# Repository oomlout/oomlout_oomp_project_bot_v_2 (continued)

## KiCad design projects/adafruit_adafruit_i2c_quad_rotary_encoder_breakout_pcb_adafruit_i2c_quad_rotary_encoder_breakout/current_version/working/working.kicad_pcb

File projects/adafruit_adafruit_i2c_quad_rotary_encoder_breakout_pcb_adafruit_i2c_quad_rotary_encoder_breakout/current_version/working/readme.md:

# adafruit_i2c_quad_rotary_encoder_breakout_pcb
 
## summary 
* id: adafruit_adafruit_i2c_quad_rotary_encoder_breakout_pcb_adafruit_i2c_quad_rotary_encoder_breakout
* user: adafruit
* name: adafruit_i2c_quad_rotary_encoder_breakout_pcb
* board: adafruit_i2c_quad_rotary_encoder_breakout
* repo: https://github.com/adafruit/Adafruit-I2C-Quad-Rotary-Encoder-Breakout-PCB

* src_file_repo_sch: 
* src_file_repo_sch_link: https://github.com/adafruit/Adafruit-I2C-Quad-Rotary-Encoder-Breakout-PCB/tree/main/
* full details link: https://github.com/oomlout/oomlout_oomp_project_bot_v_2/tree/main/projects/adafruit_adafruit_i2c_quad_rotary_encoder_breakout_pcb_adafruit_i2c_quad_rotary_encoder_breakout/current_version/working  

## schematic  
  
[schematic (pdf)](working_schematic.pdf) 

## pcb  

[board (pdf)](working.pdf)  

## working_bom
| Id | Designator | Footprint | Quantity | Designation | Supplier and ref |  | None | 
| --- | --- | --- | --- | --- | --- | --- | --- | 
| 1 | PLABEL9 | PLABEL9 | 1 |  |  |  | [''] | 
| 2 | D2 | CHIPLED_0603_NOOUTLINE | 1 | GREEN |  |  | [''] | 
| 3 | PLABEL10 | PLABEL10 | 1 |  |  |  | [''] | 
| 4 | CONN4,CONN3 | JST_SH4_RA | 2 | STEMMA_I2C_QTRA |  |  | [''] | 
| 5 | U$3,U$21,U$17,U$19 | MOUNTINGHOLE_2.5_PLATED | 4 | MOUNTINGHOLE2.5 |  |  | [''] | 
| 6 | JP1,JP5 | 1X06_ROUND_70 | 2 |  |  |  | [''] | 
| 7 | C1,C7,C5,C6 | 0603-NO | 4 | 1uF |  |  | [''] | 
| 8 | R7,R6,R9,R4,R3,R8,R1,R5,R2 | 0603-NO | 9 | 10K |  |  | [''] | 
| 9 | FID1,FID2 | FIDUCIAL_1MM | 2 | FIDUCIAL_1MM |  |  | [''] | 
| 10 | U$9,U$2 | ADAFRUIT_3.5MM | 2 |  |  |  | [''] | 
| 11 | D1 | CHIPLED_0603_NOOUTLINE | 1 | RED |  |  | [''] | 
| 12 | PLABEL13 | PLABEL13 | 1 |  |  |  | [''] | 
| 13 | C4 | 0603-NO | 1 | 0.1uF |  |  | [''] | 
| 14 | PLABEL7 | PLABEL7 | 1 |  |  |  | [''] | 
| 15 | U$25 | PCBFEAT-REV-040 | 1 |  |  |  | [''] | 
| 16 | PLABEL6 | PLABEL6 | 1 |  |  |  | [''] | 
| 17 | PLABEL14 | PLABEL14 | 1 |  |  |  | [''] | 
| 18 | PLABEL11 | PLABEL11 | 1 |  |  |  | [''] | 
| 19 | C2,C3 | 0805-NO | 2 | 10uF |  |  | [''] | 
| 20 | PLABEL15 | PLABEL15 | 1 |  |  |  | [''] | 
| 21 | PLABEL16 | PLABEL16 | 1 |  |  |  | [''] | 
| 22 | A1,A0,A2 | SOLDERJUMPER_CLOSEDWIRE | 3 |  |  |  | [''] | 
| 23 | PLABEL8 | PLABEL8 | 1 |  |  |  | [''] | 
| 24 | PLABEL0 | PLABEL0 | 1 |  |  |  | [''] | 
| 25 | PLABEL5 | PLABEL5 | 1 |  |  |  | [''] | 
| 26 | IC1 | QFN24_4MM | 1 | ATTINY8X7-MU |  |  | [''] | 
| 27 | PLABEL1 | PLABEL1 | 1 |  |  |  | [''] | 
| 28 | U$30,U$31 | STEMMAQT | 2 |  |  |  | [''] | 
| 29 | PLABEL4 | PLABEL4 | 1 |  |  |  | [''] | 
| 30 | PLABEL2 | PLABEL2 | 1 |  |  |  | [''] | 
| 31 | PLABEL12 | PLABEL12 | 1 |  |  |  | [''] | 
| 32 | PLABEL3 | PLABEL3 | 1 |  |  |  | [''] | 
| 33 | LED1,LED3,LED2,LED4 | NEO3535_REVERSE | 4 | WS2812B_SK6812E |  |  | [''] | 
| 34 | PLABEL20 | PLABEL20 | 1 |  |  |  | [''] | 
| 35 | PLABEL29 | PLABEL29 | 1 |  |  |  | [''] | 
| 36 | ENC4,ENC3,ENC2,ENC1 | PEC11+SWITCH | 4 |  |  |  | [''] | 
| 37 | PLABEL24 | PLABEL24 | 1 |  |  |  | [''] | 
| 38 | PLABEL27 | PLABEL27 | 1 |  |  |  | [''] | 
| 39 | PLABEL19 | PLABEL19 | 1 |  |  |  | [''] | 
| 40 | PLABEL26 | PLABEL26 | 1 |  |  |  | [''] | 
| 41 | PLABEL28 | PLABEL28 | 1 |  |  |  | [''] | 
| 42 | PLABEL32 | PLABEL32 | 1 |  |  |  | [''] | 
| 43 | PLABEL25 | PLABEL25 | 1 |  |  |  | [''] | 
| 44 | PLABEL21 | PLABEL21 | 1 |  |  |  | [''] | 
| 45 | PLABEL31 | PLABEL31 | 1 |  |  |  | [''] | 
| 46 | PLABEL30 | PLABEL30 | 1 |  |  |  | [''] | 
| 47 | PLABEL22 | PLABEL22 | 1 |  |  |  | [''] | 
| 48 | PLABEL23 | PLABEL23 | 1 |  |  |  | [''] | 
| 49 | PLABEL18 | PLABEL18 | 1 |  |  |  | [''] | 
| 50 | PLABEL17 | PLABEL17 | 1 |  |  |  | [''] | 

## bom_schematic
| Ref | Qnty | Value | Cmp name | Footprint | Description | Vendor | DNP | 
| --- | --- | --- | --- | --- | --- | --- | --- | 
| A0, A1, A2 | 3 | SOLDERJUMPERCLOSED | SOLDERJUMPERCLOSED | working:SOLDERJUMPER_CLOSEDWIRE |  |  |  | 
| C1, C5, C6, C7 | 4 | 1uF | CAP_CERAMIC0603_NO | working:0603-NO |  |  |  | 
| C2, C3 | 2 | 10uF | CAP_CERAMIC0805-NOOUTLINE | working:0805-NO |  |  |  | 
| C4 | 1 | 0.1uF | CAP_CERAMIC0603_NO | working:0603-NO |  |  |  | 
| CONN3, CONN4 | 2 | STEMMA_I2C_QTRA | STEMMA_I2C_QTRA | working:JST_SH4_RA |  |  |  | 
| D1 | 1 | RED | LED0603_NOOUTLINE | working:CHIPLED_0603_NOOUTLINE |  |  |  | 
| D2 | 1 | GREEN | LED0603_NOOUTLINE | working:CHIPLED_0603_NOOUTLINE |  |  |  | 
| ENC1, ENC2, ENC3, ENC4 | 4 | ENCODER_PLUS_SWITCH_PEC11 | ENCODER_PLUS_SWITCH_PEC11 | working:PEC11+SWITCH |  |  |  | 
| FID1, FID2 | 2 | FIDUCIAL_1MM | FIDUCIAL_1MM | working:FIDUCIAL_1MM |  |  |  | 
| IC1 | 1 | ATTINY8X7-MU | ATTINY8X7-MU | working:QFN24_4MM |  |  |  | 
| JP1, JP5 | 2 | HEADER-1X670MIL | HEADER-1X670MIL | working:1X06_ROUND_70 |  |  |  | 
| LED1, LED2, LED3, LED4 | 4 | WS2812B_SK6812E | WS2812B_SK6812E | working:NEO3535_REVERSE |  |  |  | 
| R1, R2, R3, R4, R5, R6, R7, R8, R9 | 9 | 10K | RESISTOR_0603_NOOUT | working:0603-NO |  |  |  | 
| U$3, U$17, U$19, U$21 | 4 | MOUNTINGHOLE2.5 | MOUNTINGHOLE2.5 | working:MOUNTINGHOLE_2.5_PLATED |  |  |  | 

## mounting_holes
| x | y | package | value | ref | size | 
| --- | --- | --- | --- | --- | --- | 
| 38.1 | 16.51 | MOUNTINGHOLE_2.5_PLATED | MOUNTINGHOLE2.5 | U$3 | m3 | 
| 0.0 | 16.51 | MOUNTINGHOLE_2.5_PLATED | MOUNTINGHOLE2.5 | U$17 | m3 | 
| 38.1 | 0.0 | MOUNTINGHOLE_2.5_PLATED | MOUNTINGHOLE2.5 | U$19 | m3 | 
| 0.0 | 0.0 | MOUNTINGHOLE_2.5_PLATED | MOUNTINGHOLE2.5 | U$21 | m3 |

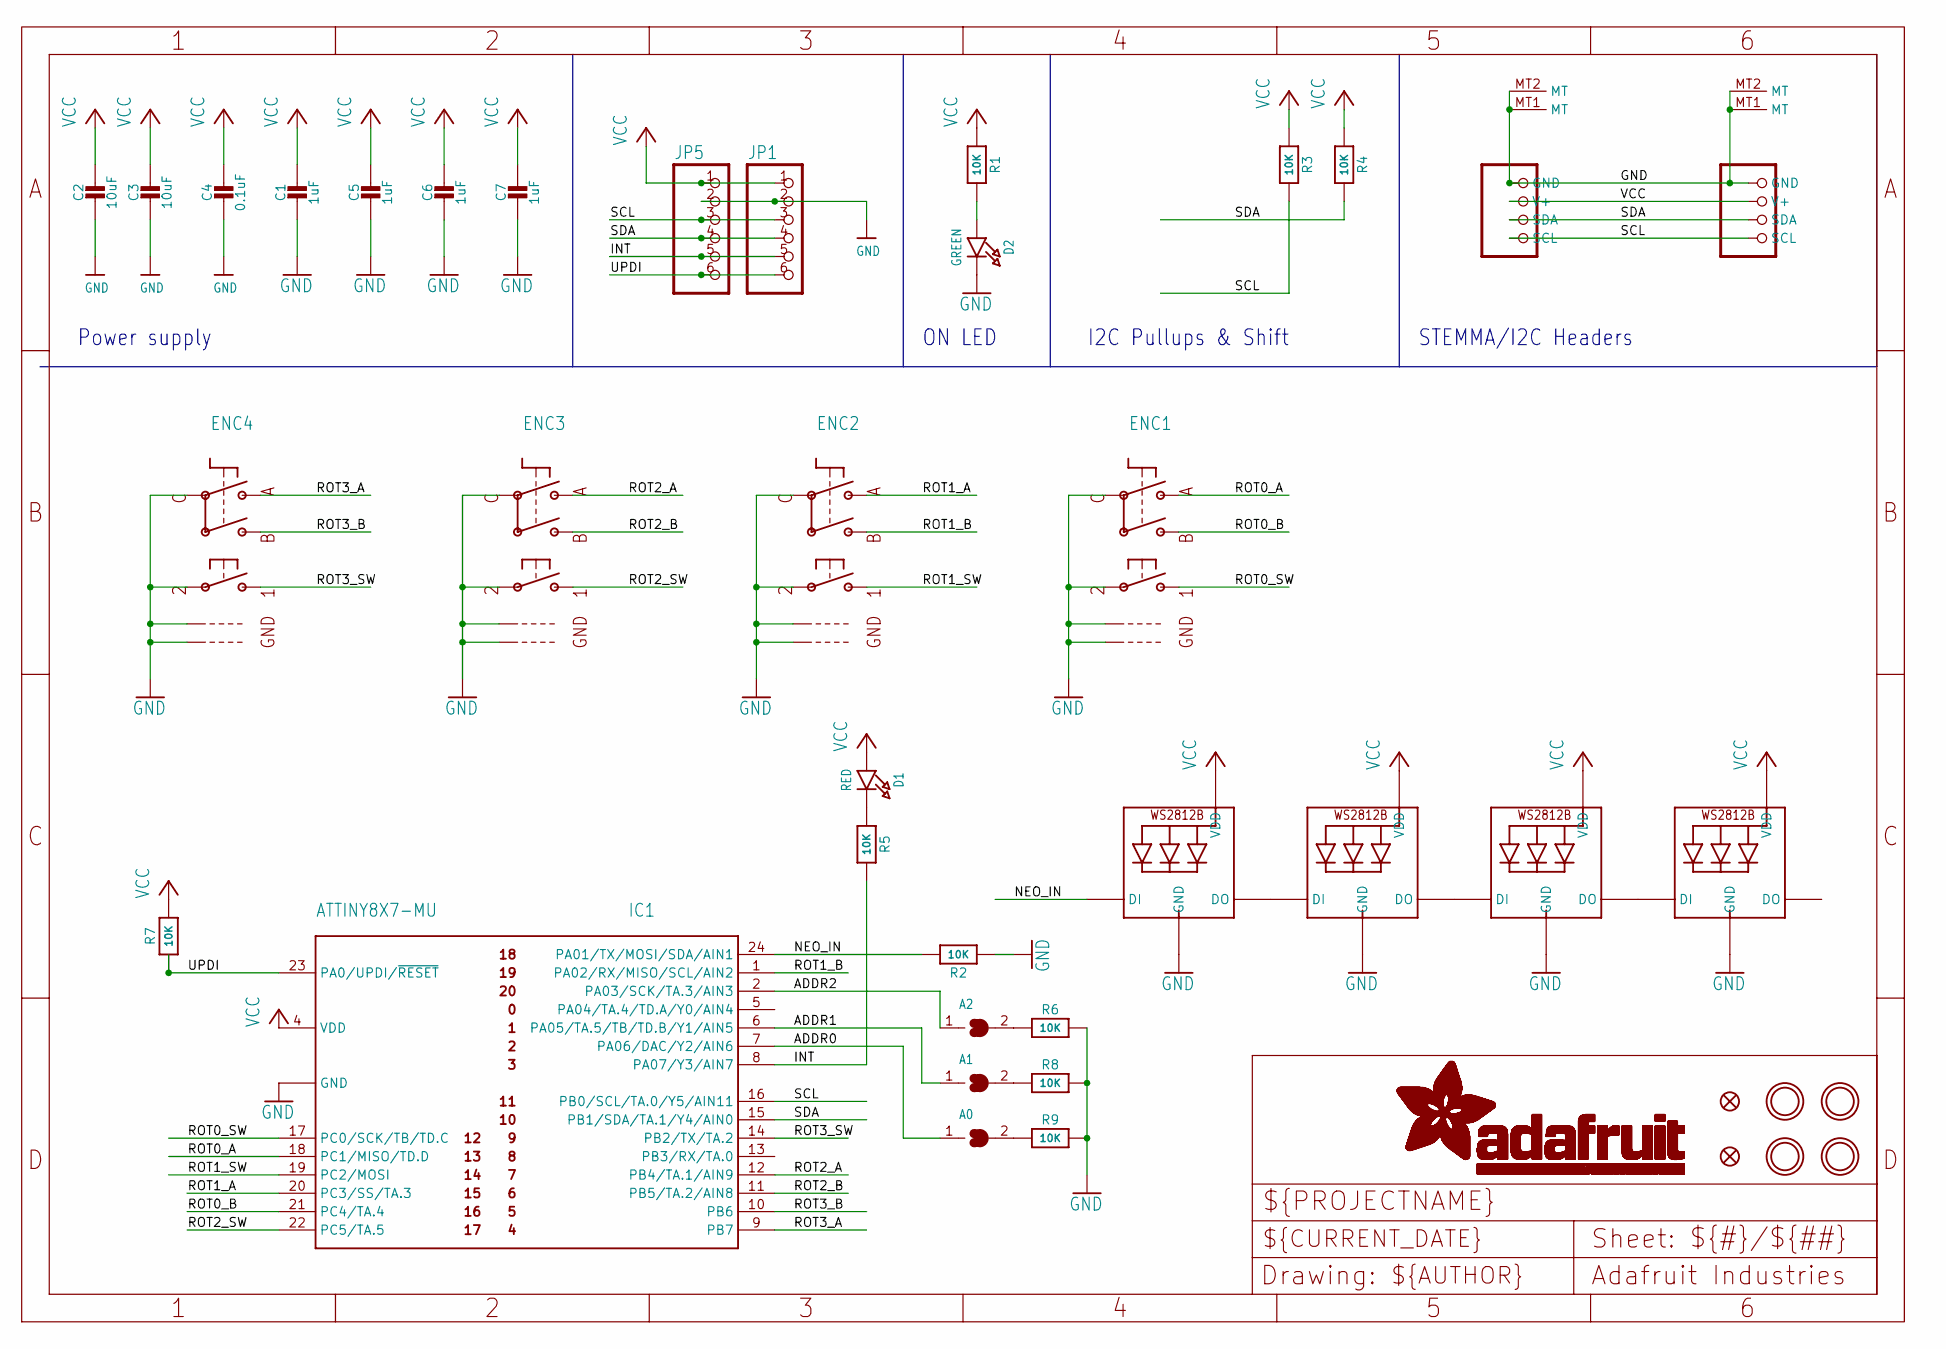
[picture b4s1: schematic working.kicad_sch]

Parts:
A0, A1, A2: SOLDERJUMPERCLOSED; SOLDERJUMPER_CLOSEDWIRE
C1, C5, C6, C7: 1uF; 0603-NO
C2, C3: 10uF; 0805-NO
C4: 0.1uF; 0603-NO
CONN3, CONN4: STEMMA_I2C_QTRA; JST_SH4_RA
D1: RED; CHIPLED_0603_NOOUTLINE
D2: GREEN; CHIPLED_0603_NOOUTLINE
ENC1, ENC2, ENC3, ENC4: ENCODER_PLUS_SWITCH_PEC11; PEC11+SWITCH
FID1, FID2: FIDUCIAL_1MM
IC1: ATTINY8X7-MU; QFN24_4MM
JP1, JP5: HEADER-1X670MIL; 1X06_ROUND_70
LED1, LED2, LED3, LED4: WS2812B_SK6812E; NEO3535_REVERSE
R1, R2, R3, R4, R5, R6, R7, R8, R9: 10K; 0603-NO
U$3, U$17, U$19, U$21: MOUNTINGHOLE2.5; MOUNTINGHOLE_2.5_PLATED

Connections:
ADDR0: A0.1, IC1.7 (PA06/DAC/Y2/AIN6)
ADDR1: A1.1, IC1.6 (PA05/TA.5/TB/TD.B/Y1/AIN5)
ADDR2: A2.1, IC1.2 (PA03/SCK/TA.3/AIN3)
GND: C1.2, C2.2, C3.2, C4.2, C5.2, C6.2, C7.2, CONN3.1 (GND), CONN3.MT1 (MT), CONN3.MT2 (MT), CONN4.1 (GND), CONN4.MT1 (MT), CONN4.MT2 (MT), D2.C, ENC1.P$2, ENC1.P$C, ENC1.P$GND1, ENC1.P$GND2, ENC2.P$2, ENC2.P$C, ENC2.P$GND1, ENC2.P$GND2, ENC3.P$2, ENC3.P$C, ENC3.P$GND1, ENC3.P$GND2, ENC4.P$2, ENC4.P$C, ENC4.P$GND1, ENC4.P$GND2, IC1.3 (GND), IC1.THERM (GND), JP1.2, JP5.2, LED1.3-GND (GND), LED2.3-GND (GND), LED3.3-GND (GND), LED4.3-GND (GND), R2.1, R6.2, R8.2, R9.2
INT: IC1.8 (PA07/Y3/AIN7), JP1.5, JP5.5, R5.2
unnamed: D2.A, R1.2
unnamed: LED1.2-DOUT (DO), LED2.4-DIN (DI)
unnamed: LED2.2-DOUT (DO), LED3.4-DIN (DI)
unnamed: LED3.2-DOUT (DO), LED4.4-DIN (DI)
unnamed: D1.C, R5.1
unnamed: A2.2, R6.1
unnamed: A1.2, R8.1
unnamed: A0.2, R9.1
NEO_IN: IC1.24 (PA01/TX/MOSI/SDA/AIN1), LED1.4-DIN (DI), R2.2
ROT0_A: ENC1.P$A, IC1.18 (PC1/MISO/TD.D)
ROT0_B: ENC1.P$B, IC1.21 (PC4/TA.4)
ROT0_SW: ENC1.P$1, IC1.17 (PC0/SCK/TB/TD.C)
ROT1_A: ENC2.P$A, IC1.20 (PC3/SS/TA.3)
ROT1_B: ENC2.P$B, IC1.1 (PA02/RX/MISO/SCL/AIN2)
ROT1_SW: ENC2.P$1, IC1.19 (PC2/MOSI)
ROT2_A: ENC3.P$A, IC1.12 (PB4/TA.1/AIN9)
ROT2_B: ENC3.P$B, IC1.11 (PB5/TA.2/AIN8)
ROT2_SW: ENC3.P$1, IC1.22 (PC5/TA.5)
ROT3_A: ENC4.P$A, IC1.9 (PB7)
ROT3_B: ENC4.P$B, IC1.10 (PB6)
ROT3_SW: ENC4.P$1, IC1.14 (PB2/TX/TA.2)
SCL: CONN3.4 (SCL), CONN4.4 (SCL), IC1.16 (PB0/SCL/TA.0/Y5/AIN11), JP1.3, JP5.3, R3.2
SDA: CONN3.3 (SDA), CONN4.3 (SDA), IC1.15 (PB1/SDA/TA.1/Y4/AIN0), JP1.4, JP5.4, R4.2
UPDI: IC1.23 (PA0/UPDI/~RESET), JP1.6, JP5.6, R7.1
VCC: C1.1, C2.1, C3.1, C4.1, C5.1, C6.1, C7.1, CONN3.2 (V+), CONN4.2 (V+), D1.A, IC1.4 (VDD), JP1.1, JP5.1, LED1.1-VDD (VDD), LED2.1-VDD (VDD), LED3.1-VDD (VDD), LED4.1-VDD (VDD), R1.1, R3.1, R4.1, R7.2

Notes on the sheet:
STEMMA/I2C Headers
I2C Pullups & Shift
Power supply
ON LED

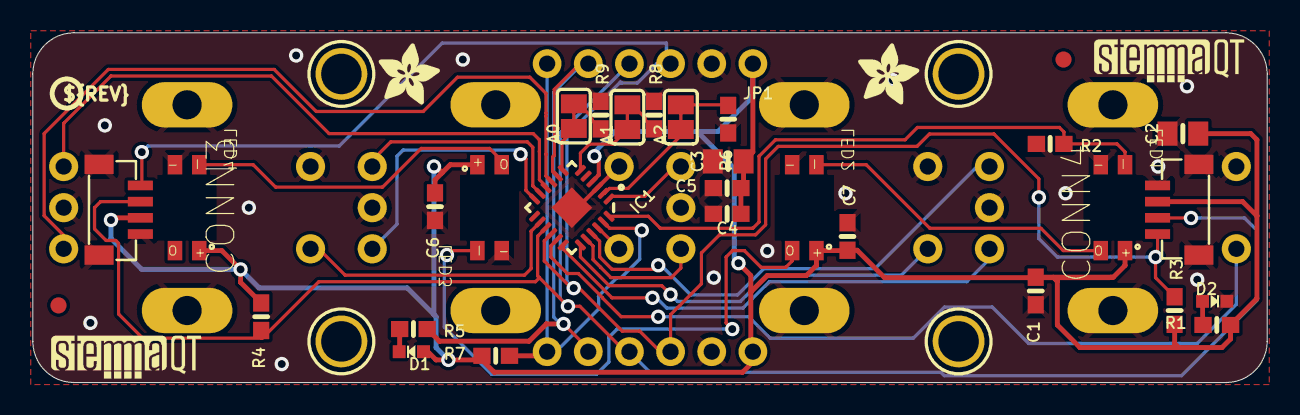
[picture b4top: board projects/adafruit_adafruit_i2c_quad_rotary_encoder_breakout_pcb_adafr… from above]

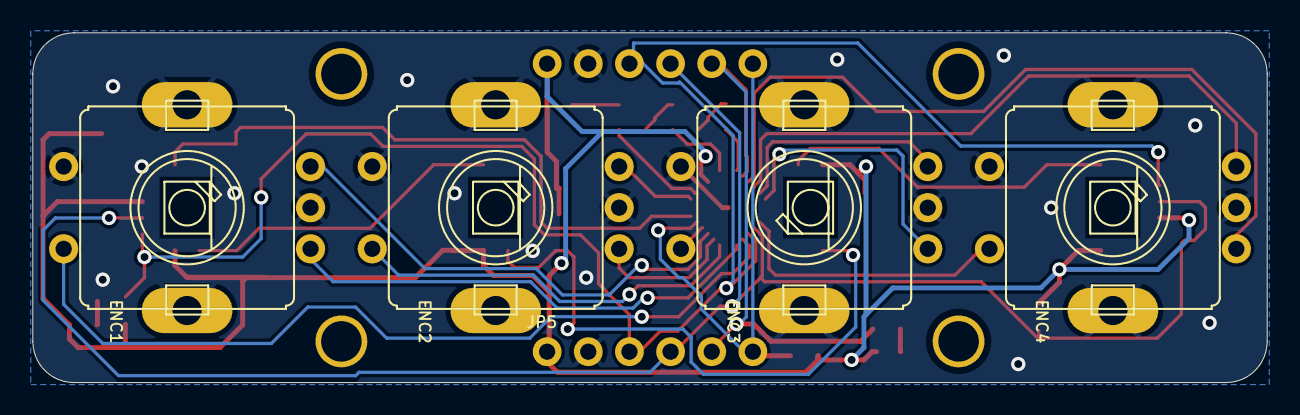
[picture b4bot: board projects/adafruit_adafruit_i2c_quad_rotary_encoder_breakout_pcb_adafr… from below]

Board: 2 copper layers, 76.2 x 21.6 mm, 78 parts (25 on the bottom side), 30 nets.

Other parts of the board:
PLABEL0: PLABEL0
PLABEL1: PLABEL1
PLABEL2: PLABEL2
PLABEL3: PLABEL3
PLABEL4: PLABEL4
PLABEL5: PLABEL5
PLABEL6: PLABEL6
PLABEL7: PLABEL7
PLABEL8: PLABEL8
PLABEL9: PLABEL9
PLABEL10: PLABEL10
PLABEL11: PLABEL11
PLABEL12: PLABEL12
PLABEL13: PLABEL13
PLABEL14: PLABEL14
PLABEL15: PLABEL15
PLABEL16: PLABEL16
PLABEL17: PLABEL17
PLABEL18: PLABEL18
PLABEL19: PLABEL19
PLABEL20: PLABEL20
PLABEL21: PLABEL21
PLABEL22: PLABEL22
PLABEL23: PLABEL23
PLABEL24: PLABEL24
PLABEL25: PLABEL25
PLABEL26: PLABEL26
PLABEL27: PLABEL27
PLABEL28: PLABEL28
PLABEL29: PLABEL29
PLABEL30: PLABEL30
PLABEL31: PLABEL31
PLABEL32: PLABEL32
U$2, U$9: ADAFRUIT_3.5MM
U$25: PCBFEAT-REV-040
U$30, U$31: STEMMAQT

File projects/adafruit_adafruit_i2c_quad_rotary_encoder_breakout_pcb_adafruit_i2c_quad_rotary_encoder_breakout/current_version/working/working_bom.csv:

"Id";"Designator";"Footprint";"Quantity";"Designation";"Supplier and ref";
1;"PLABEL9";"PLABEL9";1;"";;;
2;"D2";"CHIPLED_0603_NOOUTLINE";1;"GREEN";;;
3;"PLABEL10";"PLABEL10";1;"";;;
4;"CONN4,CONN3";"JST_SH4_RA";2;"STEMMA_I2C_QTRA";;;
5;"U$3,U$21,U$17,U$19";"MOUNTINGHOLE_2.5_PLATED";4;"MOUNTINGHOLE2.5";;;
6;"JP1,JP5";"1X06_ROUND_70";2;"";;;
7;"C1,C7,C5,C6";"0603-NO";4;"1uF";;;
8;"R7,R6,R9,R4,R3,R8,R1,R5,R2";"0603-NO";9;"10K";;;
9;"FID1,FID2";"FIDUCIAL_1MM";2;"FIDUCIAL_1MM";;;
10;"U$9,U$2";"ADAFRUIT_3.5MM";2;"";;;
11;"D1";"CHIPLED_0603_NOOUTLINE";1;"RED";;;
12;"PLABEL13";"PLABEL13";1;"";;;
13;"C4";"0603-NO";1;"0.1uF";;;
14;"PLABEL7";"PLABEL7";1;"";;;
15;"U$25";"PCBFEAT-REV-040";1;"";;;
16;"PLABEL6";"PLABEL6";1;"";;;
17;"PLABEL14";"PLABEL14";1;"";;;
18;"PLABEL11";"PLABEL11";1;"";;;
19;"C2,C3";"0805-NO";2;"10uF";;;
20;"PLABEL15";"PLABEL15";1;"";;;
21;"PLABEL16";"PLABEL16";1;"";;;
22;"A1,A0,A2";"SOLDERJUMPER_CLOSEDWIRE";3;"";;;
23;"PLABEL8";"PLABEL8";1;"";;;
24;"PLABEL0";"PLABEL0";1;"";;;
25;"PLABEL5";"PLABEL5";1;"";;;
26;"IC1";"QFN24_4MM";1;"ATTINY8X7-MU";;;
27;"PLABEL1";"PLABEL1";1;"";;;
28;"U$30,U$31";"STEMMAQT";2;"";;;
29;"PLABEL4";"PLABEL4";1;"";;;
30;"PLABEL2";"PLABEL2";1;"";;;
31;"PLABEL12";"PLABEL12";1;"";;;
32;"PLABEL3";"PLABEL3";1;"";;;
33;"LED1,LED3,LED2,LED4";"NEO3535_REVERSE";4;"WS2812B_SK6812E";;;
34;"PLABEL20";"PLABEL20";1;"";;;
35;"PLABEL29";"PLABEL29";1;"";;;
36;"ENC4,ENC3,ENC2,ENC1";"PEC11+SWITCH";4;"";;;
37;"PLABEL24";"PLABEL24";1;"";;;
38;"PLABEL27";"PLABEL27";1;"";;;
39;"PLABEL19";"PLABEL19";1;"";;;
40;"PLABEL26";"PLABEL26";1;"";;;
41;"PLABEL28";"PLABEL28";1;"";;;
42;"PLABEL32";"PLABEL32";1;"";;;
43;"PLABEL25";"PLABEL25";1;"";;;
44;"PLABEL21";"PLABEL21";1;"";;;
45;"PLABEL31";"PLABEL31";1;"";;;
46;"PLABEL30";"PLABEL30";1;"";;;
47;"PLABEL22";"PLABEL22";1;"";;;
48;"PLABEL23";"PLABEL23";1;"";;;
49;"PLABEL18";"PLABEL18";1;"";;;
50;"PLABEL17";"PLABEL17";1;"";;;

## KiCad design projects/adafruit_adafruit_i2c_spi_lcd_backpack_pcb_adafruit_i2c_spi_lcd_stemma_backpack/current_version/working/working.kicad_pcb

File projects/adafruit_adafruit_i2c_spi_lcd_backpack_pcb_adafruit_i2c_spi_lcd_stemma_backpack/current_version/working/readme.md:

# adafruit_i2c_spi_lcd_backpack_pcb
 
## summary 
* id: adafruit_adafruit_i2c_spi_lcd_backpack_pcb_adafruit_i2c_spi_lcd_stemma_backpack
* user: adafruit
* name: adafruit_i2c_spi_lcd_backpack_pcb
* board: adafruit_i2c_spi_lcd_stemma_backpack
* repo: https://github.com/adafruit/Adafruit-I2C-SPI-LCD-Backpack-PCB

* src_file_repo_sch: 
* src_file_repo_sch_link: https://github.com/adafruit/Adafruit-I2C-SPI-LCD-Backpack-PCB/tree/master/
* full details link: https://github.com/oomlout/oomlout_oomp_project_bot_v_2/tree/main/projects/adafruit_adafruit_i2c_spi_lcd_backpack_pcb_adafruit_i2c_spi_lcd_stemma_backpack/current_version/working  

## schematic  
  
[schematic (pdf)](working_schematic.pdf) 

## pcb  

[board (pdf)](working.pdf)  

## working_bom
| Id | Designator | Footprint | Quantity | Designation | Supplier and ref |  | None | 
| --- | --- | --- | --- | --- | --- | --- | --- | 
| 1 | A0,A1,A2,SPIEN0 | SOLDERJUMPER_ARROW_NOPASTE | 4 |  |  |  | [''] | 
| 2 | PLABEL3 | PLABEL3 | 1 |  |  |  | [''] | 
| 3 | PLABEL2 | PLABEL2 | 1 |  |  |  | [''] | 
| 4 | U$1,U$2 | FIDUCIAL_1MM | 2 | FIDUCIAL |  |  | [''] | 
| 5 | C1,C2 | 0603-NO | 2 | 0.1uF |  |  | [''] | 
| 6 | PLABEL4 | PLABEL4 | 1 |  |  |  | [''] | 
| 7 | CONN4,CONN3 | JST_SH4 | 2 | STEMMA_I2C_QT |  |  | [''] | 
| 8 | R1,R6 | 0603-NO | 2 | 10K |  |  | [''] | 
| 9 | PLABEL5 | PLABEL5 | 1 |  |  |  | [''] | 
| 10 | R8,R3 | RESPACK_4X0603 | 2 | 4.7K Pack |  |  | [''] | 
| 11 | PLABEL0 | PLABEL0 | 1 |  |  |  | [''] | 
| 12 | PLABEL8 | PLABEL8 | 1 |  |  |  | [''] | 
| 13 | SJ1 | SOLDERJUMPER_CLOSEDWIRE | 1 |  |  |  | [''] | 
| 14 | PLABEL1 | PLABEL1 | 1 |  |  |  | [''] | 
| 15 | D1 | CHIPLED_0603_NOOUTLINE | 1 | GREEN |  |  | [''] | 
| 16 | C5,C4 | 0805-NO | 2 | 10uF |  |  | [''] | 
| 17 | PLABEL7 | PLABEL7 | 1 |  |  |  | [''] | 
| 18 | U$4 | ADAFRUIT_3.5MM | 1 |  |  |  | [''] | 
| 19 | U$7 | PCBFEAT-REV-040 | 1 |  |  |  | [''] | 
| 20 | PLABEL11 | PLABEL11 | 1 |  |  |  | [''] | 
| 21 | J1 | 1X05-3.5MM | 1 | 1X5 |  |  | [''] | 
| 22 | JP1 | 1X16 | 1 |  |  |  | [''] | 
| 23 | C6 | 0805-NO | 1 | 1uF |  |  | [''] | 
| 24 | IC3 | SOT23-6 | 1 | AP3602/RT9361 |  |  | [''] | 
| 25 | Q2,Q1 | SOT363 | 2 | BSS138 |  |  | [''] | 
| 26 | PLABEL9 | PLABEL9 | 1 |  |  |  | [''] | 
| 27 | IC1 | SO18W | 1 | MCP23008/SO |  |  | [''] | 
| 28 | @HOLE1,@HOLE0 |  | 2 |  |  |  | [''] | 
| 29 | PLABEL10 | PLABEL10 | 1 |  |  |  | [''] | 
| 30 | IC2 | SO16 | 1 | 74HC595D |  |  | [''] | 
| 31 | R2 | RTRIM3314J | 1 | 3314J-1-104E |  |  | [''] | 
| 32 | PLABEL6 | PLABEL6 | 1 |  |  |  | [''] | 
| 33 | TP2,TP4,TP3,TP1 | TESTPOINT_ROUND_1.5MM | 4 |  |  |  | [''] | 
| 34 | U$11,U$12 | STEMMAQT | 2 |  |  |  | [''] | 
| 35 | PLABEL12 | PLABEL12 | 1 |  |  |  | [''] | 
| 36 | U$23 | ADAFRUIT_TEXT_20MM | 1 |  |  |  | [''] | 

## bom_schematic
| Ref | Qnty | Value | Cmp name | Footprint | Description | Vendor | DNP | 
| --- | --- | --- | --- | --- | --- | --- | --- | 
| A0, A1, A2 | 3 | SOLDERJUMPER | SOLDERJUMPER | working:SOLDERJUMPER_ARROW_NOPASTE |  |  |  | 
| C1, C2 | 2 | 0.1uF | CAP_CERAMIC0603_NO | working:0603-NO |  |  |  | 
| C4, C5 | 2 | 10uF | CAP_CERAMIC0805-NOOUTLINE | working:0805-NO |  |  |  | 
| C6 | 1 | 1uF | CAP_CERAMIC0805-NOOUTLINE | working:0805-NO |  |  |  | 
| CONN3, CONN4 | 2 | STEMMA_I2C_QT | STEMMA_I2C_QT | working:JST_SH4 |  |  |  | 
| D1 | 1 | GREEN | LED0603_NOOUTLINE | working:CHIPLED_0603_NOOUTLINE |  |  |  | 
| IC1 | 1 | MCP23008/SO | MCP23008/SO | working:SO18W |  |  |  | 
| IC2 | 1 | 74595D | 74595D | working:SO16 |  |  |  | 
| IC3 | 1 | AP3602 | AP3602 | working:SOT23-6 |  |  |  | 
| J1 | 1 | 1X5 | 1X5 | working:1X05-3.5MM |  |  |  | 
| JP1 | 1 | PINHD-1X16 | PINHD-1X16 | working:1X16 |  |  |  | 
| Q1, Q2 | 2 | BSS138 | MOSFET-N_DUAL | working:SOT363 |  |  |  | 
| R1, R6 | 2 | 10K | RESISTOR_0603_NOOUT | working:0603-NO |  |  |  | 
| R2 | 1 | 3314J-1-104E | R-TRIMM3314J | working:RTRIM3314J |  |  |  | 
| R3, R8 | 2 | 4.7K Pack | RESISTOR_4PACK | working:RESPACK_4X0603 |  |  |  | 
| SJ1 | 1 | SOLDERJUMPERCLOSED | SOLDERJUMPERCLOSED | working:SOLDERJUMPER_CLOSEDWIRE |  |  |  | 
| SPIEN0 | 1 | SOLDERJUMPER | SOLDERJUMPER | working:SOLDERJUMPER_ARROW_NOPASTE |  |  |  | 
| TP1, TP2, TP3, TP4 | 4 | TESTPOINTROUND1.5MM | TESTPOINTROUND1.5MM | working:TESTPOINT_ROUND_1.5MM |  |  |  | 
| U$1, U$2 | 2 | FIDUCIAL | FIDUCIAL | working:FIDUCIAL_1MM |  |  |  |

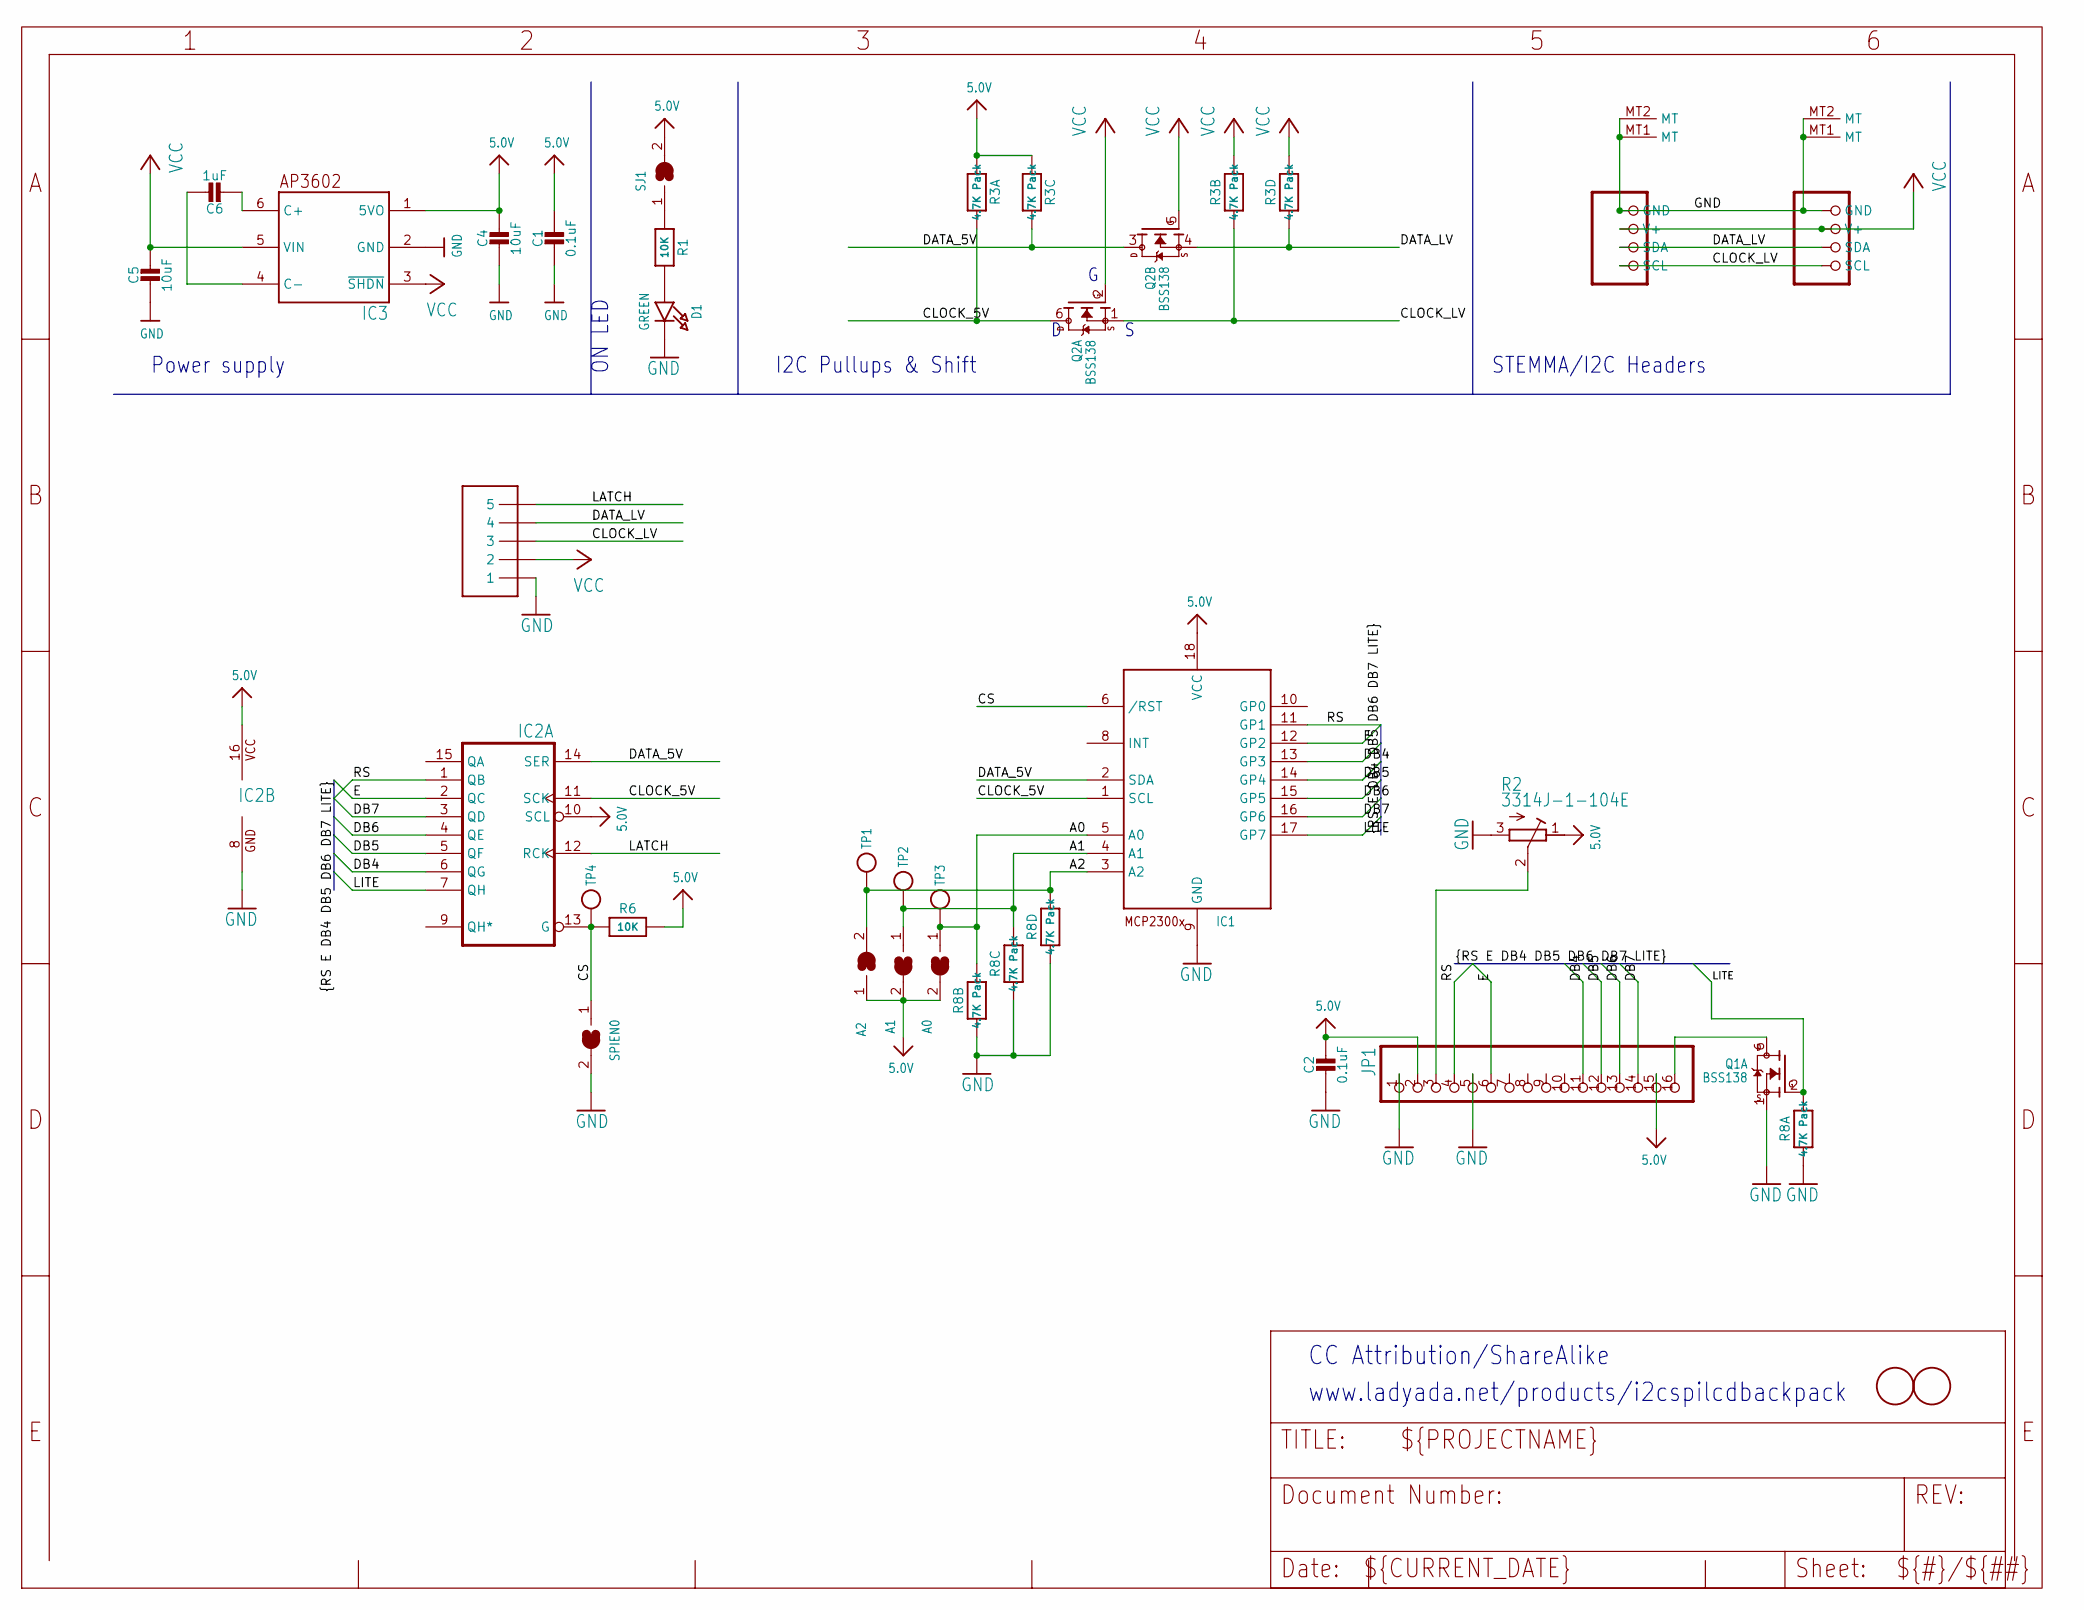
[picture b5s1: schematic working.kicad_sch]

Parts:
A0, A1, A2: SOLDERJUMPER; SOLDERJUMPER_ARROW_NOPASTE
C1, C2: 0.1uF; 0603-NO
C4, C5: 10uF; 0805-NO
C6: 1uF; 0805-NO
CONN3, CONN4: STEMMA_I2C_QT; JST_SH4
D1: GREEN; CHIPLED_0603_NOOUTLINE
IC1: MCP23008/SO; SO18W
IC2: 74595D; SO16
IC3: AP3602; SOT23-6
J1: 1X5; 1X05-3.5MM
JP1: PINHD-1X16; 1X16
Q1, Q2: BSS138; SOT363
R1, R6: 10K; 0603-NO
R2: 3314J-1-104E; RTRIM3314J
R3, R8: 4.7K Pack; RESPACK_4X0603
SJ1: SOLDERJUMPERCLOSED; SOLDERJUMPER_CLOSEDWIRE
SPIEN0: SOLDERJUMPER; SOLDERJUMPER_ARROW_NOPASTE
TP1, TP2, TP3, TP4: TESTPOINTROUND1.5MM; TESTPOINT_ROUND_1.5MM
U$1, U$2: FIDUCIAL; FIDUCIAL_1MM

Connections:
5.0V: A0.2, A1.2, A2.1, C1.1, C2.1, C4.1, IC1.18 (VCC), IC2.10 (SCL), IC2.16 (VCC), IC3.1 (5VO), JP1.2, JP1.15, R2.1 (E), R3.1, R3.3 (1), R6.1, SJ1.2
A0: A0.1, IC1.5 (A0), R8.7 (2), TP3.P$1
A1: A1.1, IC1.4 (A1), R8.6 (2), TP2.P$1
A2: A2.2, IC1.3 (A2), R8.5 (2), TP1.P$1
CLOCK_5V: IC1.1 (SCL), IC2.11 (SCK), Q2.6 (D), R3.8 (2)
CLOCK_LV: CONN3.4 (SCL), CONN4.4 (SCL), J1.3, Q2.1 (S), R3.7 (2)
CONTRAST: JP1.3, R2.2 (S)
CS: IC1.6 (/RST), IC2.13 (G), R6.2, SPIEN0.1, TP4.P$1
DATA_5V: IC1.2 (SDA), IC2.14 (SER), Q2.3 (D), R3.6 (2)
DATA_LV: CONN3.3 (SDA), CONN4.3 (SDA), J1.4, Q2.4 (S), R3.5 (2)
DB4: IC1.13 (GP3), IC2.6 (QG), JP1.11
DB5: IC1.14 (GP4), IC2.5 (QF), JP1.12
DB6: IC1.15 (GP5), IC2.4 (QE), JP1.13
DB7: IC1.16 (GP6), IC2.3 (QD), JP1.14
E: IC1.12 (GP2), IC2.2 (QC), JP1.6
GND: C1.2, C2.2, C4.2, C5.2, CONN3.1 (GND), CONN3.MT1 (MT), CONN3.MT2 (MT), CONN4.1 (GND), CONN4.MT1 (MT), CONN4.MT2 (MT), D1.C, IC1.9 (GND), IC2.8 (GND), IC3.2 (GND), J1.1, JP1.1, JP1.5, Q1.1 (S), R2.3 (A), R8.1, R8.2 (1), R8.3 (1), R8.4 (1), SPIEN0.2
LATCH: IC2.12 (RCK), J1.5
LEDK: JP1.16, Q1.6 (D)
LITE: IC1.17 (GP7), IC2.7 (QH), Q1.2 (G), R8.8 (2)
unnamed: D1.A, R1.2
unnamed: R1.1, SJ1.1
unnamed: C6.2, IC3.6 (C+)
unnamed: C6.1, IC3.4 (C-)
RS: IC1.11 (GP1), IC2.1 (QB), JP1.4
VCC: C5.1, CONN3.2 (V+), CONN4.2 (V+), IC3.3 (~SHDN), IC3.5 (VIN), J1.2, Q2.2 (G), Q2.5 (G), R3.2 (1), R3.4 (1)

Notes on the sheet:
I2C Pullups & Shift
ON LED
CC Attribution/ShareAlike
STEMMA/I2C Headers
www.ladyada.net/products/i2cspilcdbackpack
Power supply

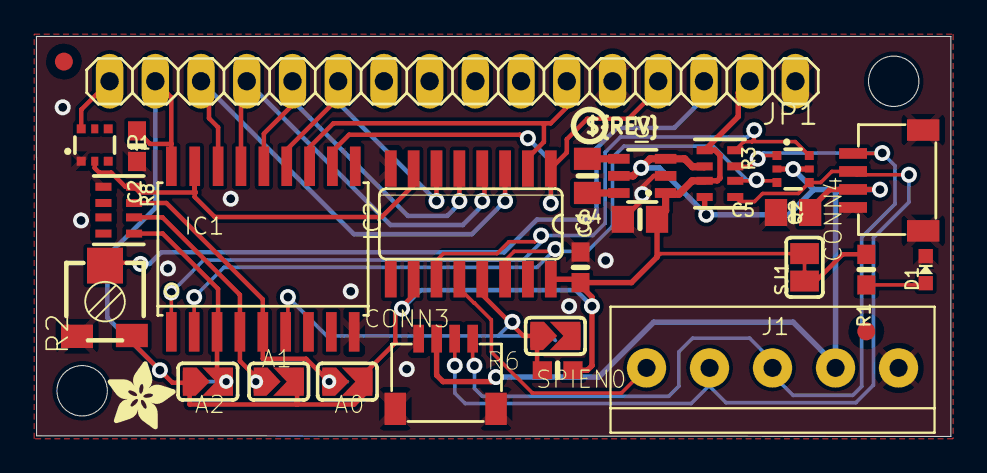
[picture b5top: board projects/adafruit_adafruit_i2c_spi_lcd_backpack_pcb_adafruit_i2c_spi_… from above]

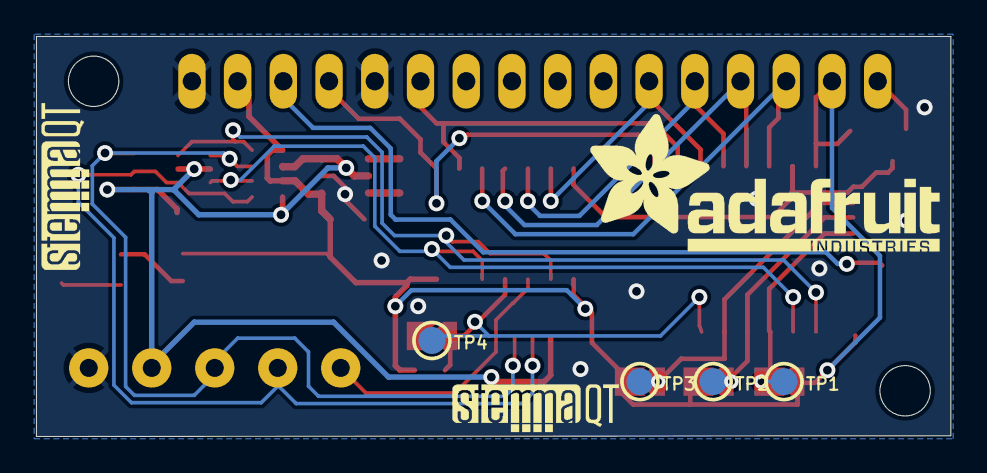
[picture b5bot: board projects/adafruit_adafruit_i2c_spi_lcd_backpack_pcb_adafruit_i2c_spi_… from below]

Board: 16 copper layers, 50.8 x 22.2 mm, 51 parts (8 on the bottom side), 25 nets.

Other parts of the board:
@HOLE0, @HOLE1: (no value)
PLABEL0: PLABEL0
PLABEL1: PLABEL1
PLABEL2: PLABEL2
PLABEL3: PLABEL3
PLABEL4: PLABEL4
PLABEL5: PLABEL5
PLABEL6: PLABEL6
PLABEL7: PLABEL7
PLABEL8: PLABEL8
PLABEL9: PLABEL9
PLABEL10: PLABEL10
PLABEL11: PLABEL11
PLABEL12: PLABEL12
U$4: ADAFRUIT_3.5MM
U$7: PCBFEAT-REV-040
U$11, U$12: STEMMAQT
U$23: ADAFRUIT_TEXT_20MM

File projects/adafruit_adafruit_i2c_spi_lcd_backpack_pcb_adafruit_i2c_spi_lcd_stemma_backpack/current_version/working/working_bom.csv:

"Id";"Designator";"Footprint";"Quantity";"Designation";"Supplier and ref";
1;"A0,A1,A2,SPIEN0";"SOLDERJUMPER_ARROW_NOPASTE";4;"";;;
2;"PLABEL3";"PLABEL3";1;"";;;
3;"PLABEL2";"PLABEL2";1;"";;;
4;"U$1,U$2";"FIDUCIAL_1MM";2;"FIDUCIAL";;;
5;"C1,C2";"0603-NO";2;"0.1uF";;;
6;"PLABEL4";"PLABEL4";1;"";;;
7;"CONN4,CONN3";"JST_SH4";2;"STEMMA_I2C_QT";;;
8;"R1,R6";"0603-NO";2;"10K";;;
9;"PLABEL5";"PLABEL5";1;"";;;
10;"R8,R3";"RESPACK_4X0603";2;"4.7K Pack";;;
11;"PLABEL0";"PLABEL0";1;"";;;
12;"PLABEL8";"PLABEL8";1;"";;;
13;"SJ1";"SOLDERJUMPER_CLOSEDWIRE";1;"";;;
14;"PLABEL1";"PLABEL1";1;"";;;
15;"D1";"CHIPLED_0603_NOOUTLINE";1;"GREEN";;;
16;"C5,C4";"0805-NO";2;"10uF";;;
17;"PLABEL7";"PLABEL7";1;"";;;
18;"U$4";"ADAFRUIT_3.5MM";1;"";;;
19;"U$7";"PCBFEAT-REV-040";1;"";;;
20;"PLABEL11";"PLABEL11";1;"";;;
21;"J1";"1X05-3.5MM";1;"1X5";;;
22;"JP1";"1X16";1;"";;;
23;"C6";"0805-NO";1;"1uF";;;
24;"IC3";"SOT23-6";1;"AP3602/RT9361";;;
25;"Q2,Q1";"SOT363";2;"BSS138";;;
26;"PLABEL9";"PLABEL9";1;"";;;
27;"IC1";"SO18W";1;"MCP23008/SO";;;
28;"@HOLE1,@HOLE0";"";2;"";;;
29;"PLABEL10";"PLABEL10";1;"";;;
30;"IC2";"SO16";1;"74HC595D";;;
31;"R2";"RTRIM3314J";1;"3314J-1-104E";;;
32;"PLABEL6";"PLABEL6";1;"";;;
33;"TP2,TP4,TP3,TP1";"TESTPOINT_ROUND_1.5MM";4;"";;;
34;"U$11,U$12";"STEMMAQT";2;"";;;
35;"PLABEL12";"PLABEL12";1;"";;;
36;"U$23";"ADAFRUIT_TEXT_20MM";1;"";;;

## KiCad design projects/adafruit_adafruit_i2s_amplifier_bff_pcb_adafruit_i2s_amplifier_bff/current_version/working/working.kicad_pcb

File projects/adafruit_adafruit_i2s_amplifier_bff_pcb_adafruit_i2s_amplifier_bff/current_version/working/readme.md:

# adafruit_i2s_amplifier_bff_pcb
 
## summary 
* id: adafruit_adafruit_i2s_amplifier_bff_pcb_adafruit_i2s_amplifier_bff
* user: adafruit
* name: adafruit_i2s_amplifier_bff_pcb
* board: adafruit_i2s_amplifier_bff
* repo: https://github.com/adafruit/Adafruit-I2S-Amplifier-BFF-PCB

* src_file_repo_sch: 
* src_file_repo_sch_link: https://github.com/adafruit/Adafruit-I2S-Amplifier-BFF-PCB/tree/main/
* full details link: https://github.com/oomlout/oomlout_oomp_project_bot_v_2/tree/main/projects/adafruit_adafruit_i2s_amplifier_bff_pcb_adafruit_i2s_amplifier_bff/current_version/working  

## schematic  
  
[schematic (pdf)](working_schematic.pdf) 

## pcb  

[board (pdf)](working.pdf)  

## working_bom
| Id | Designator | Footprint | Quantity | Designation | Supplier and ref |  | None | 
| --- | --- | --- | --- | --- | --- | --- | --- | 
| 1 | U$6,U$8 | FIDUCIAL_1MM | 2 | FIDUCIAL_1MM |  |  | [''] | 
| 2 | PLABEL3 | PLABEL3 | 1 |  |  |  | [''] | 
| 3 | PLABEL8 | PLABEL8 | 1 |  |  |  | [''] | 
| 4 | SJ1,SJ2,SJ3 | SOLDERJUMPER_CLOSEDWIRE | 3 |  |  |  | [''] | 
| 5 | JP5,JP4,JP2 | 1X01_2MM | 3 |  |  |  | [''] | 
| 6 | SJ4 | SOLDERJUMPER_2WAY_OPEN_NOPASTE | 1 |  |  |  | [''] | 
| 7 | R2 | 0603-NO | 1 | 560K |  |  | [''] | 
| 8 | PLABEL23 | PLABEL23 | 1 |  |  |  | [''] | 
| 9 | PLABEL7 | PLABEL7 | 1 |  |  |  | [''] | 
| 10 | PLABEL21 | PLABEL21 | 1 |  |  |  | [''] | 
| 11 | PLABEL20 | PLABEL20 | 1 |  |  |  | [''] | 
| 12 | PLABEL14 | PLABEL14 | 1 |  |  |  | [''] | 
| 13 | FB2,FB1 | 0603-NO | 2 | Ferrite |  |  | [''] | 
| 14 | R1 | 0603-NO | 1 | 1M |  |  | [''] | 
| 15 | U1 | QFN16_3MM | 1 | MAX98357A |  |  | [''] | 
| 16 | C1 | 0603-NO | 1 | 0.1uF |  |  | [''] | 
| 17 | PLABEL5 | PLABEL5 | 1 |  |  |  | [''] | 
| 18 | U$1 | 53398-0271 | 1 | CON_MOLEX_2P |  |  | [''] | 
| 19 | C6,C5 | 0603-NO | 2 | 220pF |  |  | [''] | 
| 20 | PLABEL4 | PLABEL4 | 1 |  |  |  | [''] | 
| 21 | C2 | 0805-NO | 1 | 10uF |  |  | [''] | 
| 22 | PLABEL22 | PLABEL22 | 1 |  |  |  | [''] | 
| 23 | PLABEL12 | PLABEL12 | 1 |  |  |  | [''] | 
| 24 | PLABEL6 | PLABEL6 | 1 |  |  |  | [''] | 
| 25 | PLABEL1 | PLABEL1 | 1 |  |  |  | [''] | 
| 26 | PLABEL2 | PLABEL2 | 1 |  |  |  | [''] | 
| 27 | JP3,JP1 | 1X07_CASTEL | 2 |  |  |  | [''] | 
| 28 | PLABEL27 | PLABEL27 | 1 |  |  |  | [''] | 
| 29 | PLABEL25 | PLABEL25 | 1 |  |  |  | [''] | 
| 30 | PLABEL26 | PLABEL26 | 1 |  |  |  | [''] | 
| 31 | PLABEL24 | PLABEL24 | 1 |  |  |  | [''] | 
| 32 | PLABEL28 | PLABEL28 | 1 |  |  |  | [''] | 
| 33 | U$2 | ADAFRUIT_3.5MM | 1 |  |  |  | [''] | 
| 34 | U$3 | PCBFEAT-REV-040 | 1 |  |  |  | [''] | 
| 35 | PLABEL19 | PLABEL19 | 1 |  |  |  | [''] | 

## bom_schematic
| Ref | Qnty | Value | Cmp name | Footprint | Description | Vendor | DNP | 
| --- | --- | --- | --- | --- | --- | --- | --- | 
| C1 | 1 | 0.1uF | CAP_CERAMIC0603_NO | working:0603-NO |  |  |  | 
| C2 | 1 | 10uF | CAP_CERAMIC0805-NOOUTLINE | working:0805-NO |  |  |  | 
| C5, C6 | 2 | 220pF | CAP_CERAMIC0603_NO | working:0603-NO |  |  |  | 
| FB1, FB2 | 2 | Ferrite | FERRITE-0603NO | working:0603-NO |  |  |  | 
| JP1, JP3 | 2 | HEADER-1X7_CASTEL | HEADER-1X7_CASTEL | working:1X07_CASTEL |  |  |  | 
| JP2, JP4, JP5 | 3 | HEADER-1X12MM | HEADER-1X12MM | working:1X01_2MM |  |  |  | 
| R1 | 1 | 1M | RESISTOR_0603_NOOUT | working:0603-NO |  |  |  | 
| R2 | 1 | 560K | RESISTOR_0603_NOOUT | working:0603-NO |  |  |  | 
| SJ1, SJ2, SJ3 | 3 | SOLDERJUMPERCLOSED | SOLDERJUMPERCLOSED | working:SOLDERJUMPER_CLOSEDWIRE |  |  |  | 
| SJ4 | 1 | SOLDERJUMPER_2WAY | SOLDERJUMPER_2WAY | working:SOLDERJUMPER_2WAY_OPEN_NOPASTE |  |  |  | 
| U1 | 1 | MAX98357A | AUDIOAMP_MAX98357 | working:QFN16_3MM |  |  |  | 
| U$1 | 1 | CON_MOLEX_2P | CON_MOLEX_2P | working:53398-0271 |  |  |  | 
| U$6, U$8 | 2 | FIDUCIAL_1MM | FIDUCIAL_1MM | working:FIDUCIAL_1MM |  |  |  |

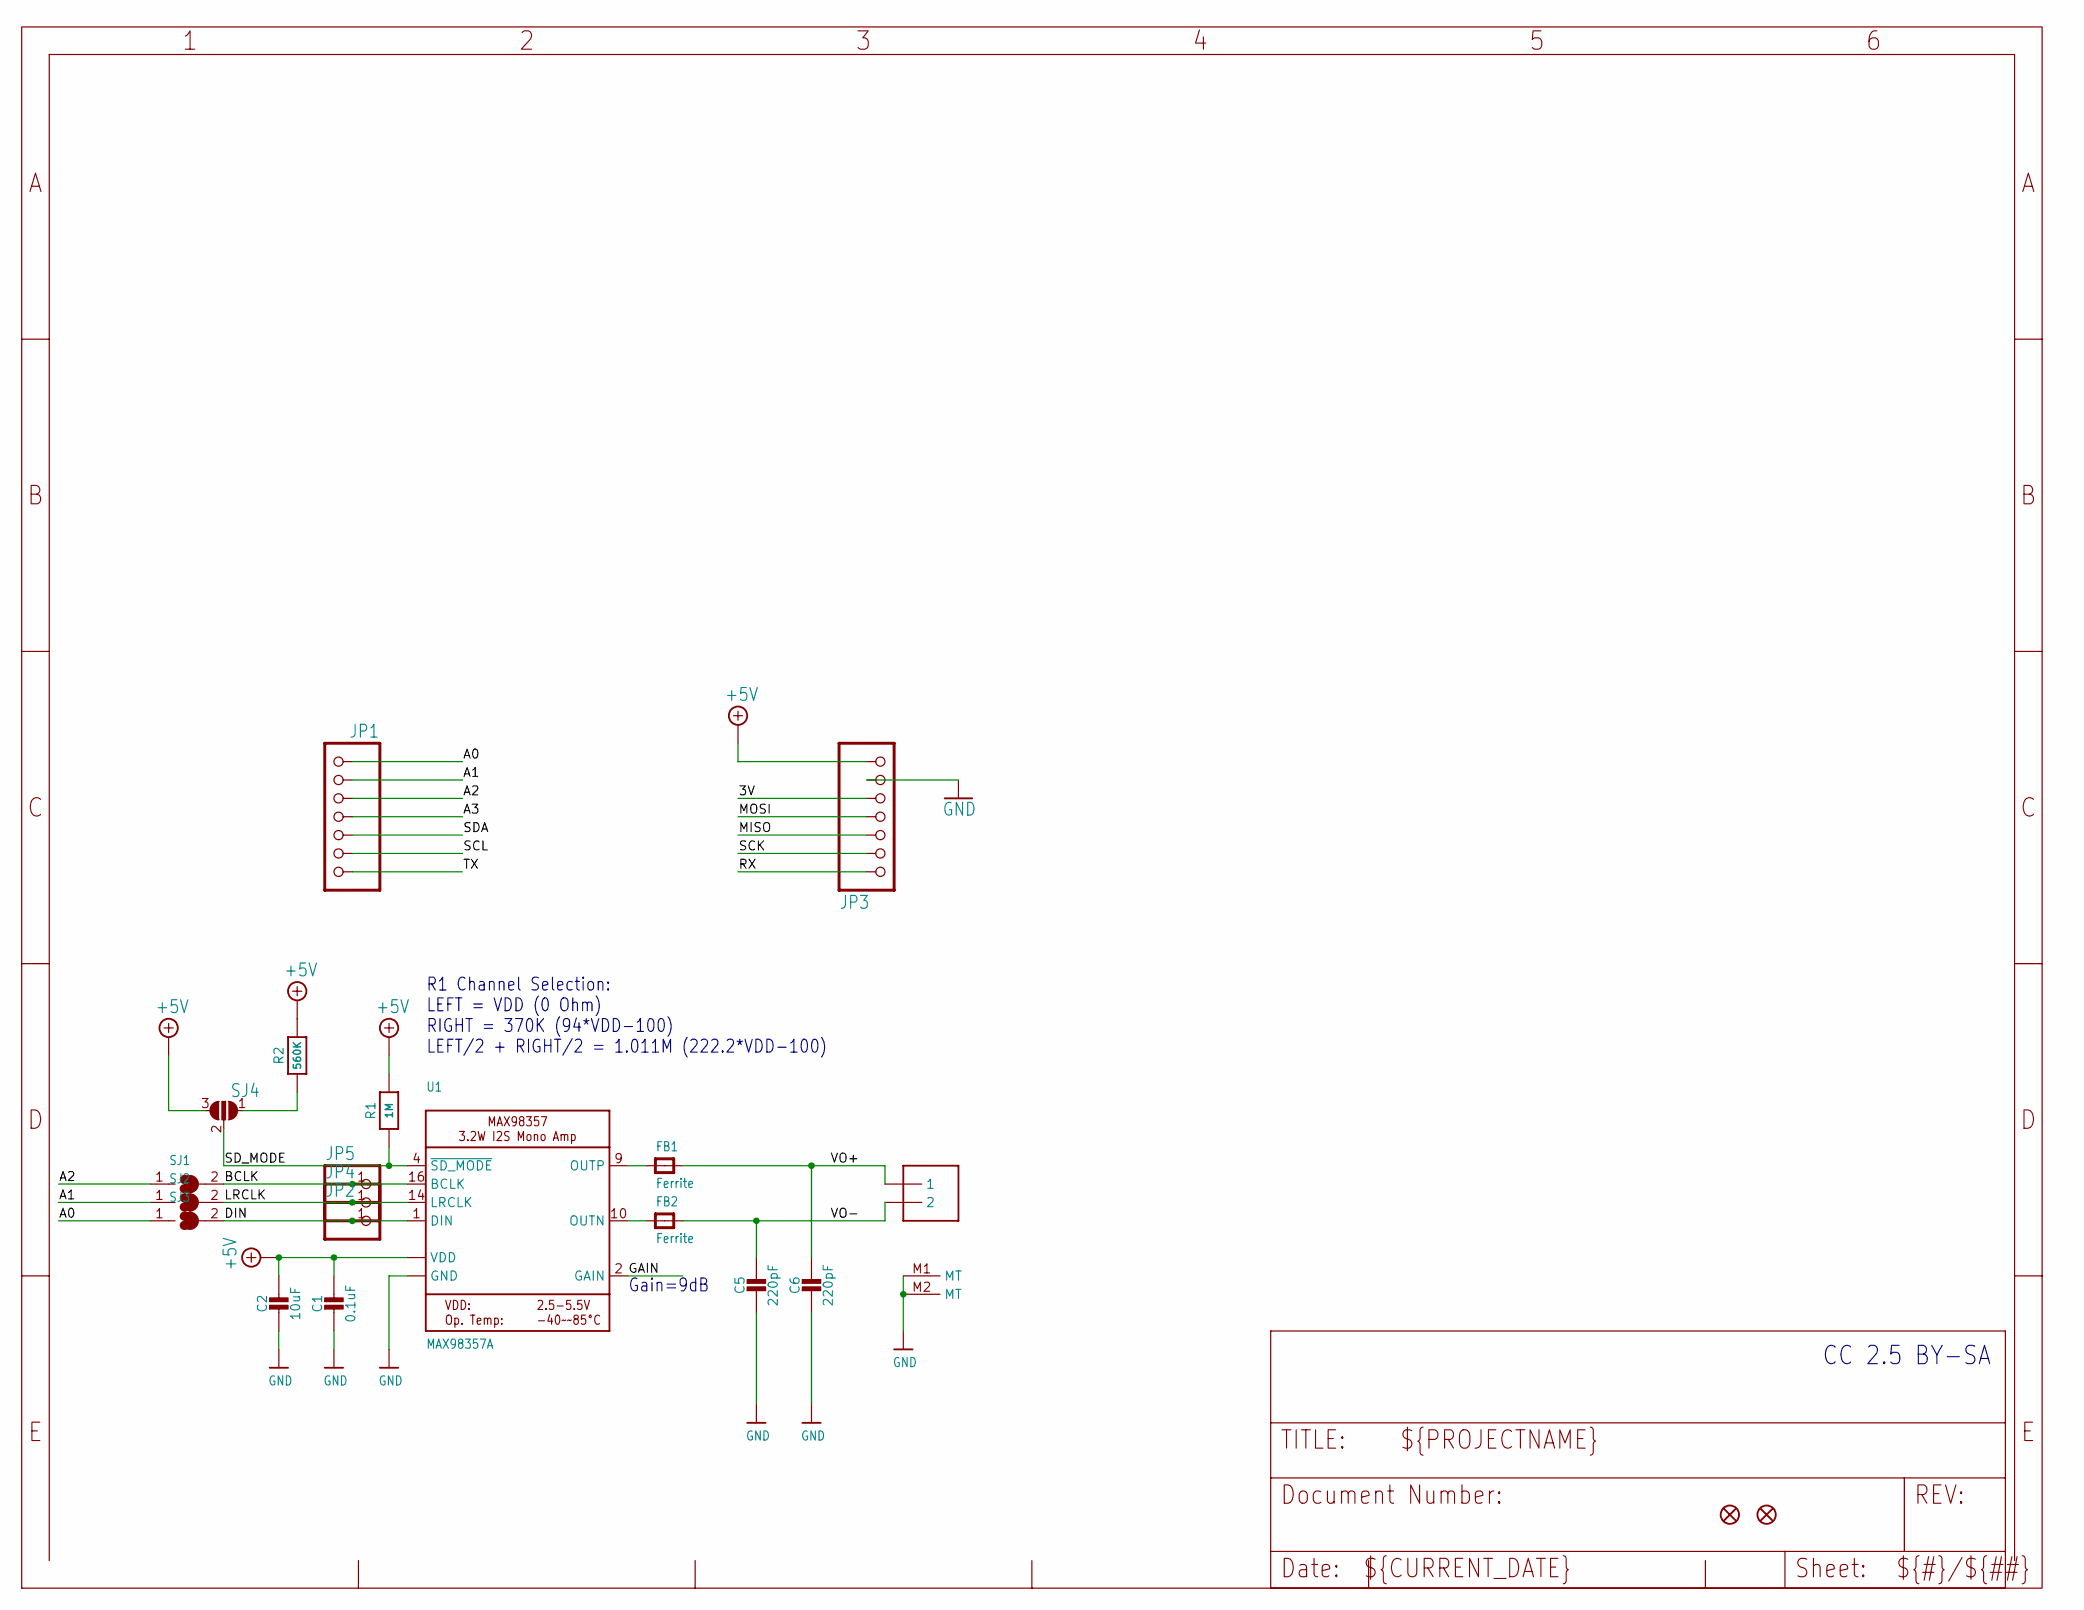
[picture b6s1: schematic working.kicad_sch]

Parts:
C1: 0.1uF; 0603-NO
C2: 10uF; 0805-NO
C5, C6: 220pF; 0603-NO
FB1, FB2: Ferrite; 0603-NO
JP1, JP3: HEADER-1X7_CASTEL; 1X07_CASTEL
JP2, JP4, JP5: HEADER-1X12MM; 1X01_2MM
R1: 1M; 0603-NO
R2: 560K; 0603-NO
SJ1, SJ2, SJ3: SOLDERJUMPERCLOSED; SOLDERJUMPER_CLOSEDWIRE
SJ4: SOLDERJUMPER_2WAY; SOLDERJUMPER_2WAY_OPEN_NOPASTE
U1: MAX98357A; QFN16_3MM
U$1: CON_MOLEX_2P; 53398-0271
U$6, U$8: FIDUCIAL_1MM

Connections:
3V: JP3.5, JP3.5C (5)
+5V: C1.1, C2.1, JP3.7, JP3.7C (7), R1.2, R2.2, SJ4.3, U1.7 (VDD), U1.8 (VDD)
A0: JP1.1, JP1.1C (1), SJ3.1
A1: JP1.2, JP1.2C (2), SJ2.1
A2: JP1.3, JP1.3C (3), SJ1.1
A3: JP1.4, JP1.4C (4)
BCLK: JP5.1, SJ1.2, U1.16 (BCLK)
DIN: JP2.1, SJ3.2, U1.1 (DIN)
GAIN: U1.2 (GAIN)
GND: C1.2, C2.2, C5.2, C6.2, JP3.6, JP3.6C (6), U1.3 (GND), U1.11 (GND), U1.15 (GND), U1.THERMAL (GND), U$1.M1 (MT), U$1.M2 (MT)
LRCLK: JP4.1, SJ2.2, U1.14 (LRCLK)
MISO: JP3.3, JP3.3C (3)
MOSI: JP3.4, JP3.4C (4)
unnamed: R2.1, SJ4.1
unnamed: FB2.1, U1.10 (OUTN)
unnamed: FB1.1, U1.9 (OUTP)
RX: JP3.1, JP3.1C (1)
SCK: JP3.2, JP3.2C (2)
SCL: JP1.6, JP1.6C (6)
SDA: JP1.5, JP1.5C (5)
SD_MODE: R1.1, SJ4.2, U1.4 (~SD_MODE)
TX: JP1.7, JP1.7C (7)
VO+: C6.1, FB1.2, U$1.1
VO-: C5.1, FB2.2, U$1.2

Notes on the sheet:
CC 2.5 BY-SA
Gain=9dB
R1 Channel Selection: LEFT = VDD (0 Ohm) RIGHT = 370K (94*VDD-100) LEFT/2 + RIGHT/2 = 1.011M (222.2*VDD-100)

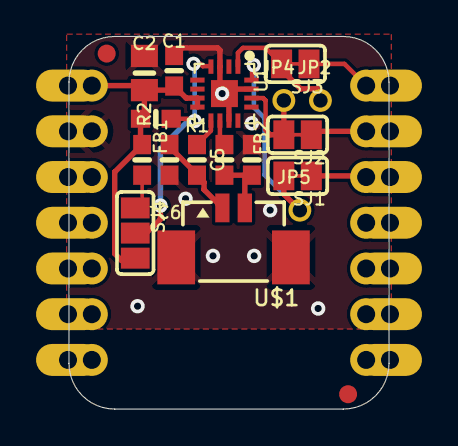
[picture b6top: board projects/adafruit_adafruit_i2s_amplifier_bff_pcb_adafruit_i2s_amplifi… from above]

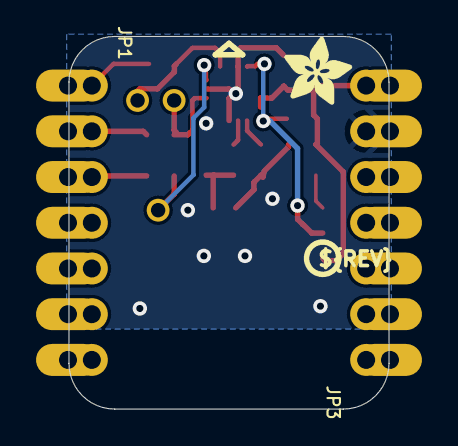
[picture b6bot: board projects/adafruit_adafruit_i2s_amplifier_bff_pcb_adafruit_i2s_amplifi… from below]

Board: 16 copper layers, 17.8 x 20.7 mm, 43 parts (10 on the bottom side), 23 nets.

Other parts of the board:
PLABEL1: PLABEL1
PLABEL2: PLABEL2
PLABEL3: PLABEL3
PLABEL4: PLABEL4
PLABEL5: PLABEL5
PLABEL6: PLABEL6
PLABEL7: PLABEL7
PLABEL8: PLABEL8
PLABEL12: PLABEL12
PLABEL14: PLABEL14
PLABEL19: PLABEL19
PLABEL20: PLABEL20
PLABEL21: PLABEL21
PLABEL22: PLABEL22
PLABEL23: PLABEL23
PLABEL24: PLABEL24
PLABEL25: PLABEL25
PLABEL26: PLABEL26
PLABEL27: PLABEL27
PLABEL28: PLABEL28
U$2: ADAFRUIT_3.5MM
U$3: PCBFEAT-REV-040
